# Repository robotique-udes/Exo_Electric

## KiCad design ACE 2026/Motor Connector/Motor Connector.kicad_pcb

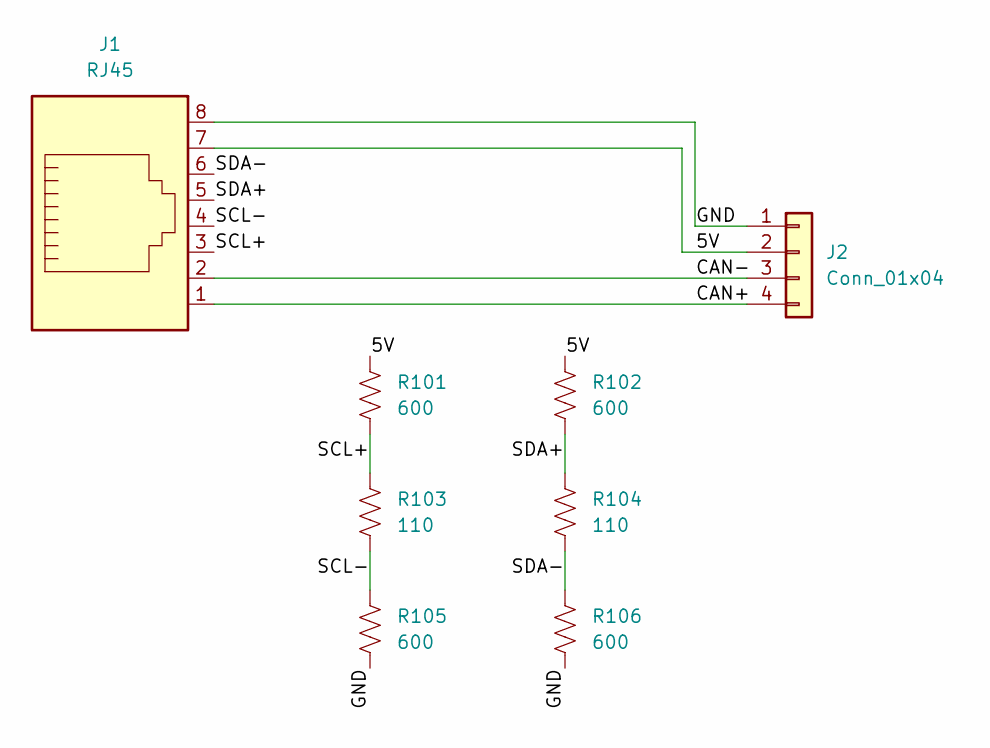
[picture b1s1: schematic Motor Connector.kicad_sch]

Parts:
J1: RJ45; RJ45_Amphenol_54602-x08_Horizontal
J2: Conn_01x04; SolderWire-0.75sqmm_1x04_P4.8mm_D1.25mm_OD2.3mm
R101, R102, R105, R106: 600; R_0805_2012Metric
R103, R104: 110; R_0805_2012Metric

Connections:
/5V: J1.7, J2.2, R101.1, R102.1
/CAN+: J1.1, J2.4
/CAN-: J1.2, J2.3
/GND: J1.8, J2.1, R105.2, R106.2
/SCL+: J1.3, R101.2, R103.1
/SCL-: J1.4, R103.2, R105.1
/SDA+: J1.5, R102.2, R104.1
/SDA-: J1.6, R104.2, R106.1

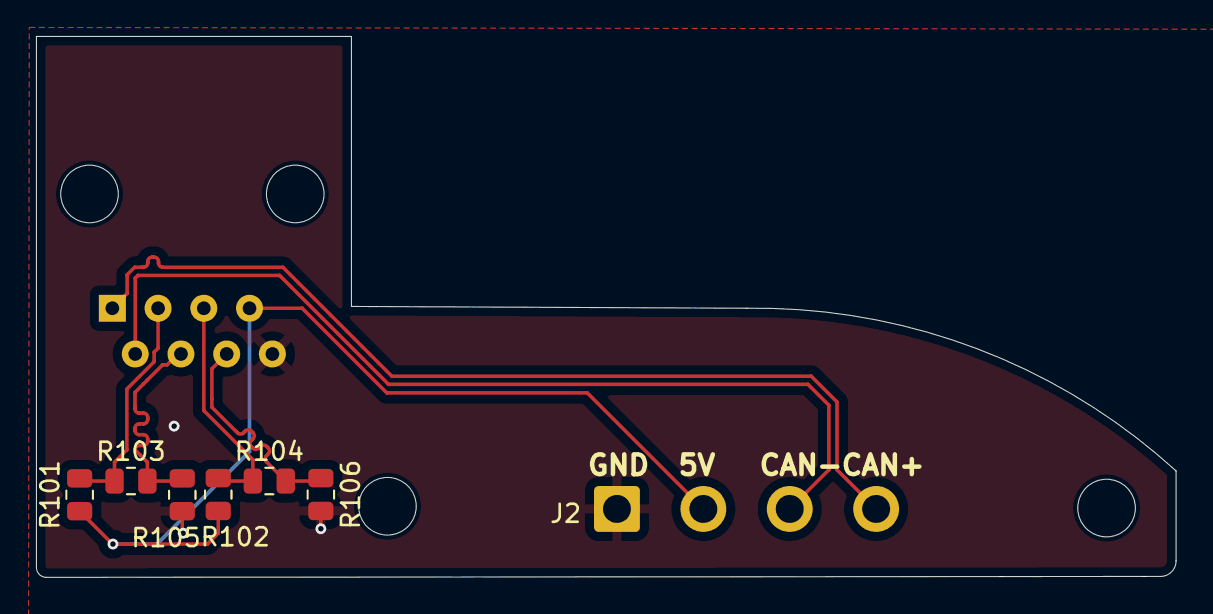
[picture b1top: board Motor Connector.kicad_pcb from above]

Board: 2 copper layers, 63.3 x 30.0 mm, 8 parts (1 on the bottom side), 8 nets.

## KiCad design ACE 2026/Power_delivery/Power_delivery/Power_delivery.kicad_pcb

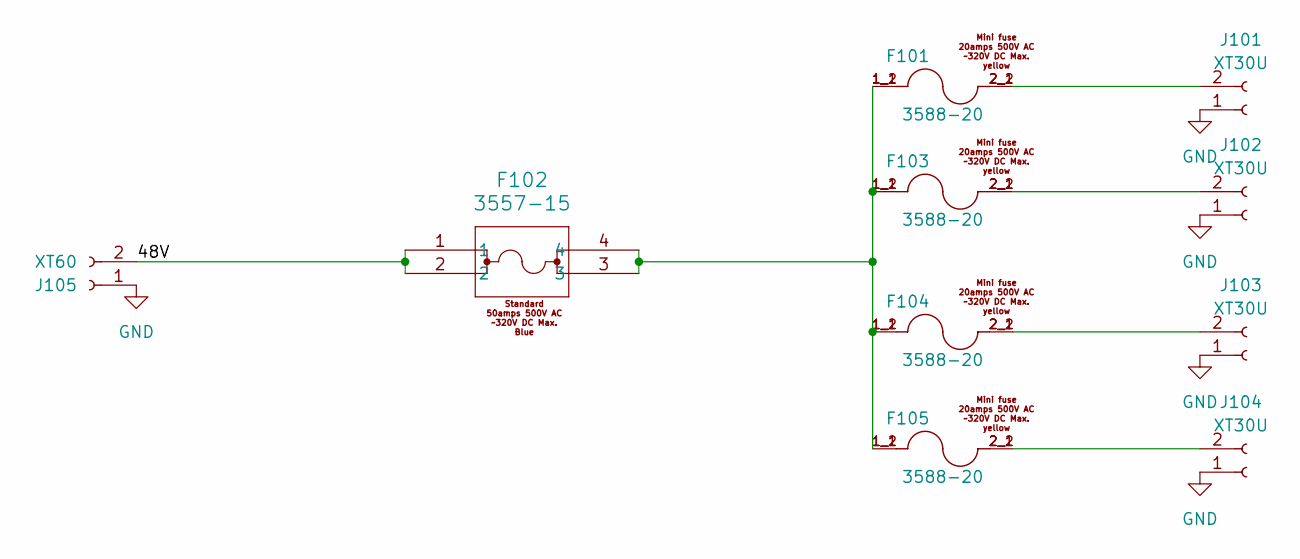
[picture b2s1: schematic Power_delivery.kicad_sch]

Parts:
F101, F103, F104, F105: 3588-20; FUSE_3588-20; PARTREV E
F102: 3557-15; 3557-15_KEY
J101, J102, J103, J104: XT30U; AMASS_XT30U-F_1x02_P5.0mm_Vertical
J105: XT60; AMASS_XT60-F_1x02_P7.20mm_Vertical

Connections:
/48V: F102.1, F102.2, J105.2
GND: J101.1, J102.1, J103.1, J104.1, J105.1
unnamed: F101.1_1, F101.1_2, F102.3, F102.4, F103.1_1, F103.1_2, F104.1_1, F104.1_2, F105.1_1, F105.1_2
unnamed: F101.2_1, F101.2_2, J101.2
unnamed: F103.2_1, F103.2_2, J102.2
unnamed: F104.2_1, F104.2_2, J103.2
unnamed: F105.2_1, F105.2_2, J104.2

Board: 4 copper layers, 10 parts (0 on the bottom side), 7 nets, no tracks yet.

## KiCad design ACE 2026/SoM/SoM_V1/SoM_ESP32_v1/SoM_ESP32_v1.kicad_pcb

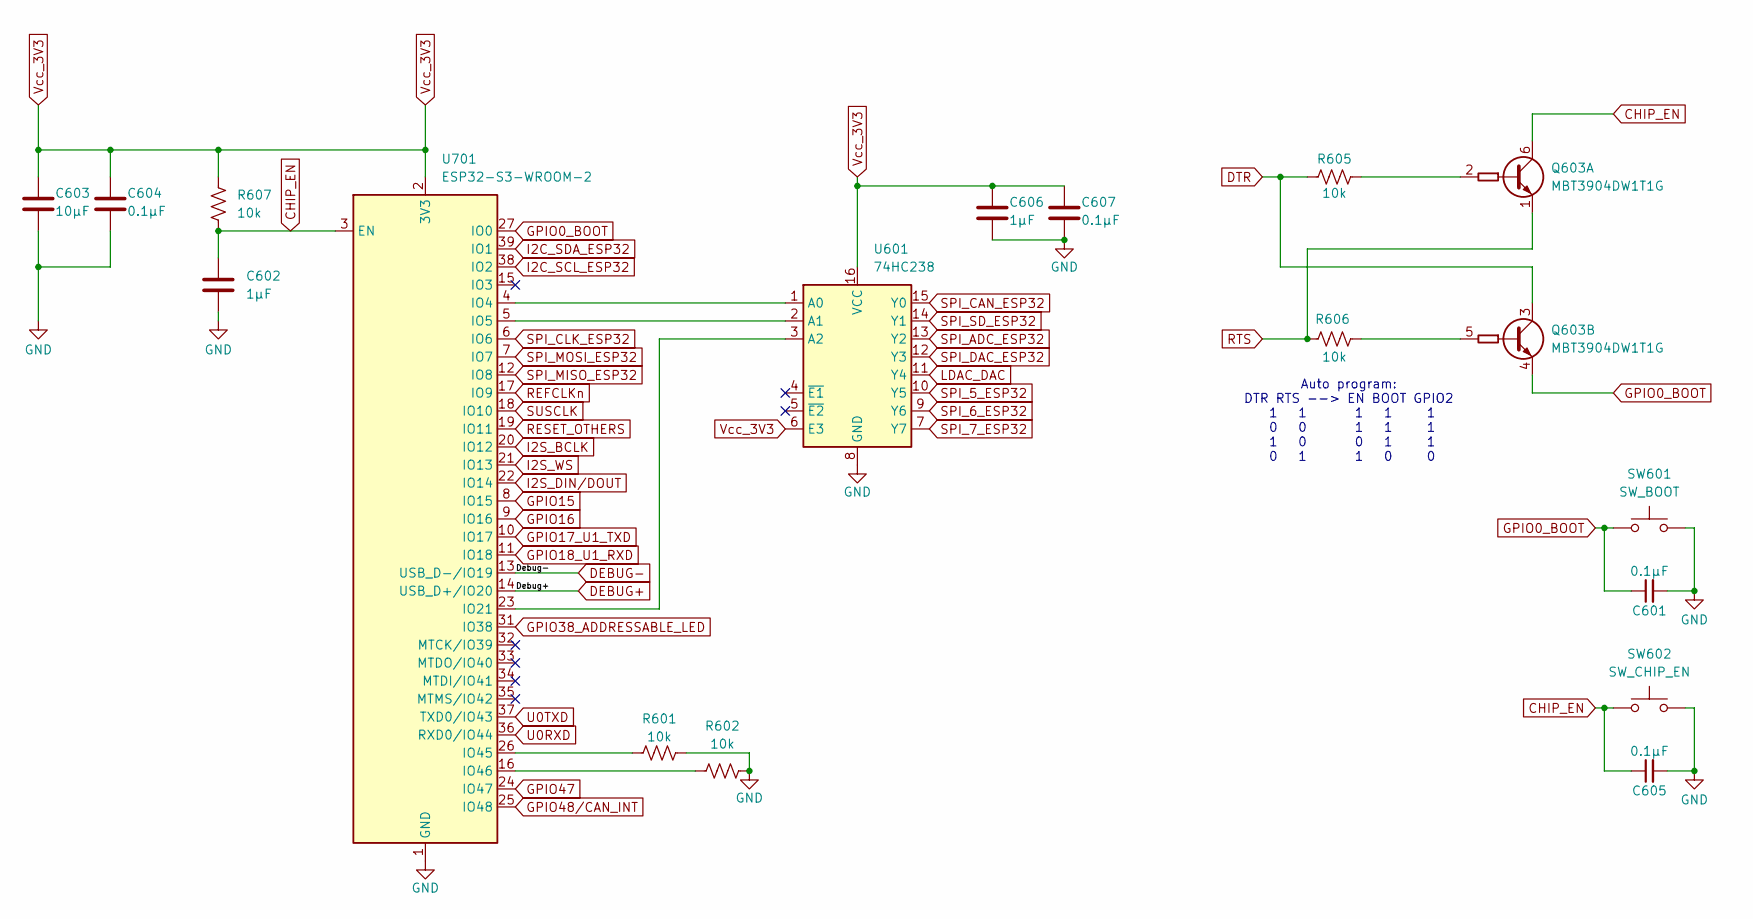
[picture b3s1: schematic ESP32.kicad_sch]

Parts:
C601, C604, C605, C607: 0.1µF; R_0805_2012Metric
C602, C606: 1µF; R_0805_2012Metric
C603: 10µF; R_0805_2012Metric
Q603: MBT3904DW1T1G; SOT-363_SC-70-6
R601, R602, R605, R606, R607: 10k; R_0805_2012Metric
SW601: SW_BOOT; SW_DIP_SPSTx01_Slide_6.7x4.1mm_W6.73mm_P2.54mm_LowProfile_J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
SW602: SW_CHIP_EN; SW_DIP_SPSTx01_Slide_6.7x4.1mm_W6.73mm_P2.54mm_LowProfile_J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
U601: 74HC238; SOIC-16_3.9x9.9mm_P1.27mm
U701: ESP32-S3-WROOM-2

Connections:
CHIP_EN: C602.1, C605.1, Q603.6 (C1), R607.2, SW602.1, U701.3 (EN); also elsewhere on the board
DEBUG+: U701.14 (USB_D+/IO20); also elsewhere on the board
DEBUG-: U701.13 (USB_D-/IO19); also elsewhere on the board
DTR: Q603.3 (C2), R605.1; also elsewhere on the board
GND: C601.2, C602.2, C603.2, C604.2, C605.2, C606.2, C607.2, R601.2, R602.2, SW601.2, SW602.2, U601.8 (GND), U701.1 (GND), U701.40 (GND), U701.41 (GND); also elsewhere on the board
GPIO0_BOOT: C601.1, Q603.4 (E2), SW601.1, U701.27 (IO0)
GPIO15: U701.8 (IO15); also elsewhere on the board
GPIO16: U701.9 (IO16); also elsewhere on the board
GPIO17_U1_TXD: U701.10 (IO17); also elsewhere on the board
GPIO18_U1_RXD: U701.11 (IO18); also elsewhere on the board
GPIO38_ADDRESSABLE_LED: U701.31 (IO38); also elsewhere on the board
GPIO47: U701.24 (IO47); also elsewhere on the board
GPIO48/CAN_INT: U701.25 (IO48); also elsewhere on the board
I2C_SCL_ESP32: U701.38 (IO2); also elsewhere on the board
I2C_SDA_ESP32: U701.39 (IO1); also elsewhere on the board
I2S_BCLK: U701.20 (IO12); also elsewhere on the board
I2S_DIN/DOUT: U701.22 (IO14); also elsewhere on the board
I2S_WS: U701.21 (IO13); also elsewhere on the board
LDAC_DAC: U601.11 (Y4); also elsewhere on the board
unnamed: Q603.2 (B1), R605.2
unnamed: Q603.5 (B2), R606.2
unnamed: U601.1 (A0), U701.4 (IO4)
unnamed: U601.2 (A1), U701.5 (IO5)
unnamed: U601.3 (A2), U701.23 (IO21)
unnamed: R601.1, U701.26 (IO45)
unnamed: R602.1, U701.16 (IO46)
REFCLKn: U701.17 (IO9)
RESET_OTHERS: U701.19 (IO11); also elsewhere on the board
RTS: Q603.1 (E1), R606.1; also elsewhere on the board
SPI_5_ESP32: U601.10 (Y5); also elsewhere on the board
SPI_6_ESP32: U601.9 (Y6); also elsewhere on the board
SPI_7_ESP32: U601.7 (Y7)
SPI_ADC_ESP32: U601.13 (Y2); also elsewhere on the board
SPI_CAN_ESP32: U601.15 (Y0); also elsewhere on the board
SPI_CLK_ESP32: U701.6 (IO6); also elsewhere on the board
SPI_DAC_ESP32: U601.12 (Y3); also elsewhere on the board
SPI_MISO_ESP32: U701.12 (IO8); also elsewhere on the board
SPI_MOSI_ESP32: U701.7 (IO7); also elsewhere on the board
SPI_SD_ESP32: U601.14 (Y1)
SUSCLK: U701.18 (IO10); also elsewhere on the board
U0RXD: U701.36 (RXD0/IO44); also elsewhere on the board
U0TXD: U701.37 (TXD0/IO43); also elsewhere on the board
Vcc_3V3: C603.1, C604.1, C606.1, C607.1, R607.1, U601.6 (E3), U601.16 (VCC), U701.2 (3V3); also elsewhere on the board

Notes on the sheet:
Auto program: DTR RTS --> EN BOOT GPIO2 1 1 1 1 1 0 0 1 1 1 1 0 0 1 1 0 1 1 0 0

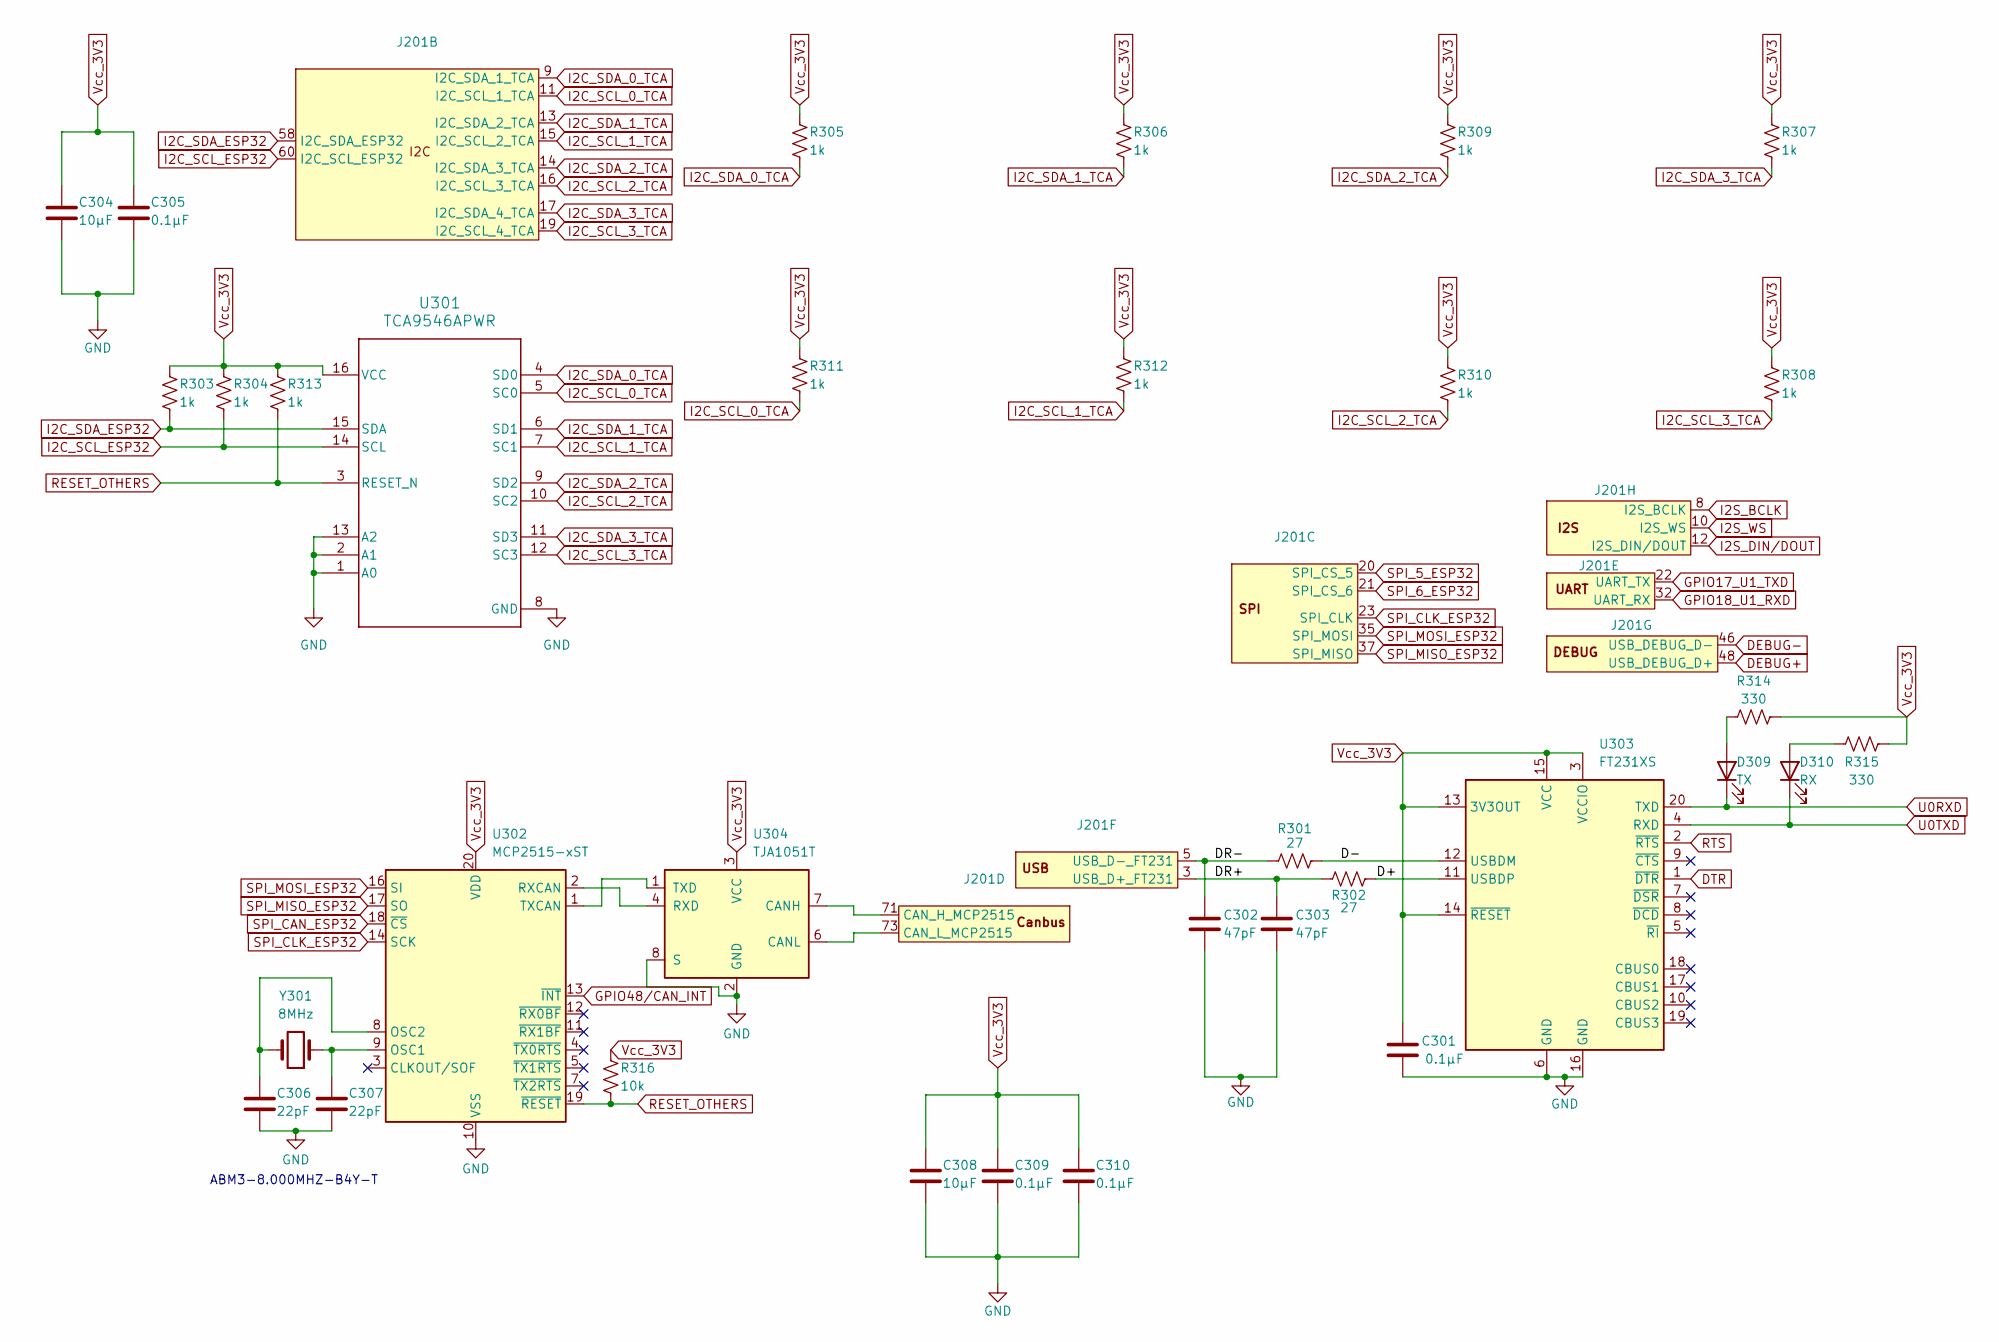
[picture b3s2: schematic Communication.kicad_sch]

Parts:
C301, C305, C309, C310: 0.1µF; R_0805_2012Metric
C302, C303: 47pF; R_0805_2012Metric
C304, C308: 10µF; R_0805_2012Metric
C306, C307: 22pF; R_0805_2012Metric
D309: TX; LED_0805_2012Metric
D310: RX; LED_0805_2012Metric
J201: NGFF_E
R301, R302: 27; R_0805_2012Metric
R303, R304, R305, R306, R307, R308, R309, R310, R311, R312, R313: 1k; R_0805_2012Metric
R314, R315: 330; R_0805_2012Metric
R316: 10k; R_0805_2012Metric
U301: TCA9546APWR; TSSOP-16_4.4x5mm_P0.65mm
U302: MCP2515-xST; TSSOP-20_4.4x6.5mm_P0.65mm
U303: FT231XS; SSOP-20_3.9x8.7mm_P0.635mm
U304: TJA1051T; SOIC-8_3.9x4.9mm_P1.27mm
Y301: 8MHz; Crystal_SMD_Abracon_ABM3-2Pin_5.0x3.2mm

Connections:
/Communication/D+: R302.2, U303.11 (USBDP)
/Communication/D-: R301.2, U303.12 (USBDM)
/Communication/DR+: C303.1, J201.3 (USB_D+_FT231), R302.1
/Communication/DR-: C302.1, J201.5 (USB_D-_FT231), R301.1
CHIP_EN: J201.56 (RESET_ESP32); also elsewhere on the board
DEBUG+: J201.48 (USB_DEBUG_D+); also elsewhere on the board
DEBUG-: J201.46 (USB_DEBUG_D-); also elsewhere on the board
DTR: U303.1 (~DTR); also elsewhere on the board
GND: C301.2, C302.2, C303.2, C304.2, C305.2, C306.2, C307.2, C308.2, C309.2, C310.2, J201.1 (GND), J201.7 (GND), J201.18 (GND), J201.33 (GND), J201.38 (GND), J201.39 (GND), J201.45 (GND), J201.51 (GND), J201.55 (GND), J201.57 (GND), J201.62 (GND), J201.63 (GND), J201.69 (GND), J201.75 (GND), U301.1 (A0), U301.2 (A1), U301.8 (GND), U301.13 (A2), U302.10 (VSS), U303.6 (GND), U303.16 (GND), U304.2 (GND), U304.8 (S); also elsewhere on the board
GPIO17_U1_TXD: J201.22 (UART_TX); also elsewhere on the board
GPIO18_U1_RXD: J201.32 (UART_RX); also elsewhere on the board
GPIO48/CAN_INT: U302.13 (~INT); also elsewhere on the board
I2C_SCL_0_TCA: J201.11 (I2C_SCL_1_TCA), R311.2, U301.5 (SC0)
I2C_SCL_1_TCA: J201.15 (I2C_SCL_2_TCA), R312.2, U301.7 (SC1)
I2C_SCL_2_TCA: J201.16 (I2C_SCL_3_TCA), R310.2, U301.10 (SC2)
I2C_SCL_3_TCA: J201.19 (I2C_SCL_4_TCA), R308.2, U301.12 (SC3)
I2C_SCL_ESP32: J201.60 (I2C_SCL_ESP32), R304.2, U301.14 (SCL); also elsewhere on the board
I2C_SDA_0_TCA: J201.9 (I2C_SDA_1_TCA), R305.2, U301.4 (SD0)
I2C_SDA_1_TCA: J201.13 (I2C_SDA_2_TCA), R306.2, U301.6 (SD1)
I2C_SDA_2_TCA: J201.14 (I2C_SDA_3_TCA), R309.2, U301.9 (SD2)
I2C_SDA_3_TCA: J201.17 (I2C_SDA_4_TCA), R307.2, U301.11 (SD3)
I2C_SDA_ESP32: J201.58 (I2C_SDA_ESP32), R303.2, U301.15 (SDA); also elsewhere on the board
I2S_BCLK: J201.8 (I2S_BCLK); also elsewhere on the board
I2S_DIN/DOUT: J201.12 (I2S_DIN/DOUT); also elsewhere on the board
I2S_WS: J201.10 (I2S_WS); also elsewhere on the board
unnamed 32: D309.2 (A), R314.1; also elsewhere on the board
unnamed 33: D310.2 (A), R315.1; also elsewhere on the board
unnamed: J201.71 (CAN_H_MCP2515), U304.7 (CANH)
unnamed: J201.73 (CAN_L_MCP2515), U304.6 (CANL)
unnamed: C307.1, U302.9 (OSC1), Y301.1
unnamed: C306.1, U302.8 (OSC2), Y301.2
unnamed: U302.2 (RXCAN), U304.4 (RXD)
unnamed: U302.1 (TXCAN), U304.1 (TXD)
RESET_OTHERS: J201.54 (RESET_AUTRES), R313.2, R316.2, U301.3 (RESET_N), U302.19 (~RESET); also elsewhere on the board
RTS: U303.2 (~RTS); also elsewhere on the board
SPI_5_ESP32: J201.20 (SPI_CS_1); also elsewhere on the board
SPI_6_ESP32: J201.21 (SPI_CS_2); also elsewhere on the board
SPI_CAN_ESP32: U302.18 (~CS); also elsewhere on the board
SPI_CLK_ESP32: J201.23 (SPI_CLK), U302.14 (SCK); also elsewhere on the board
SPI_MISO_ESP32: J201.37 (SPI_MISO), U302.17 (SO); also elsewhere on the board
SPI_MOSI_ESP32: J201.35 (SPI_MOSI), U302.16 (SI); also elsewhere on the board
U0RXD: D309.1 (K), U303.20 (TXD); also elsewhere on the board
U0TXD: D310.1 (K), U303.4 (RXD); also elsewhere on the board
Vcc_3V3: C301.1, C304.1, C305.1, C308.1, C309.1, C310.1, J201.2 (Vcc_3v3), J201.4 (Vcc_3v3), J201.72 (Vcc_3v3), J201.74 (Vcc_3v3), R303.1, R304.1, R305.1, R306.1, R307.1, R308.1, R309.1, R310.1, R311.1, R312.1, R313.1, R314.2, R315.2, R316.1, U301.16 (VCC), U302.20 (VDD), U303.3 (VCCIO), U303.13 (3V3OUT), U303.14 (~RESET), U303.15 (VCC), U304.3 (VCC); also elsewhere on the board

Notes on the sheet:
ABM3-8.000MHZ-B4Y-T

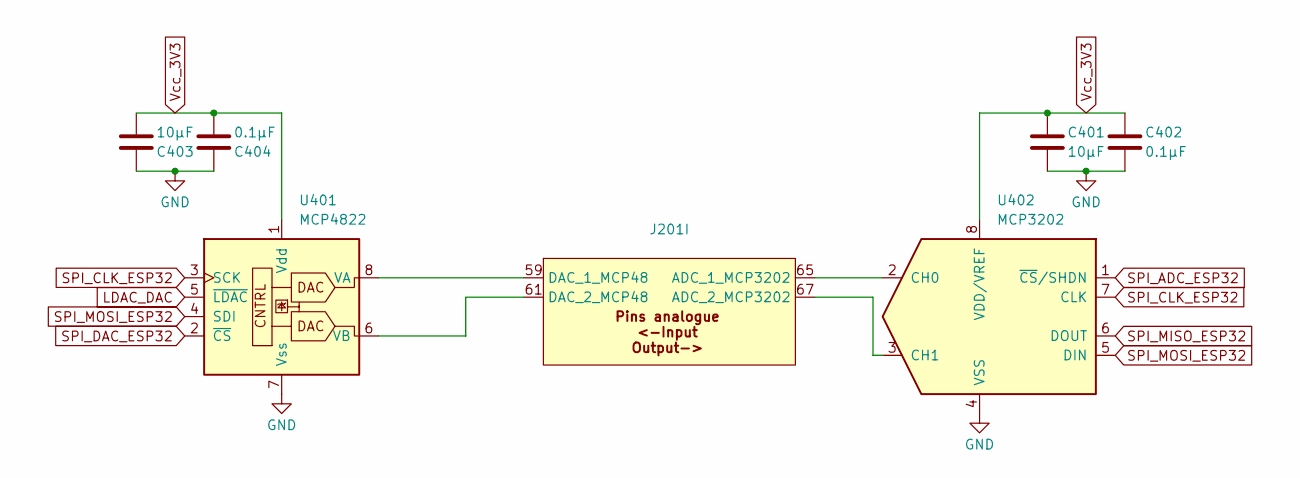
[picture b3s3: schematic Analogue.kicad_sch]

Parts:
C401, C403: 10µF; R_0805_2012Metric
C402, C404: 0.1µF; R_0805_2012Metric
J201: NGFF_E
U401: MCP4822; SOIC-8_3.9x4.9mm_P1.27mm
U402: MCP3202; SOIC-8_3.9x4.9mm_P1.27mm

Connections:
CHIP_EN: J201.56 (RESET_ESP32); also elsewhere on the board
GND: C401.2, C402.2, C403.1, C404.1, J201.1 (GND), J201.7 (GND), J201.18 (GND), J201.33 (GND), J201.38 (GND), J201.39 (GND), J201.45 (GND), J201.51 (GND), J201.55 (GND), J201.57 (GND), J201.62 (GND), J201.63 (GND), J201.69 (GND), J201.75 (GND), U401.7 (Vss), U402.4 (VSS); also elsewhere on the board
LDAC_DAC: U401.5 (~LDAC); also elsewhere on the board
unnamed: J201.65 (ADC_1_MCP3202), U402.2 (CH0)
unnamed: J201.67 (ADC_2_MCP3202), U402.3 (CH1)
unnamed: J201.59 (DAC_1_MCP48), U401.8 (VA)
unnamed: J201.61 (DAC_2_MCP48), U401.6 (VB)
RESET_OTHERS: J201.54 (RESET_AUTRES); also elsewhere on the board
SPI_ADC_ESP32: U402.1 (~CS/SHDN); also elsewhere on the board
SPI_CLK_ESP32: U401.3 (SCK), U402.7 (CLK); also elsewhere on the board
SPI_DAC_ESP32: U401.2 (~CS); also elsewhere on the board
SPI_MISO_ESP32: U402.6 (DOUT); also elsewhere on the board
SPI_MOSI_ESP32: U401.4 (SDI), U402.5 (DIN); also elsewhere on the board
Vcc_3V3: C401.1, C402.1, C403.2, C404.2, J201.2 (Vcc_3v3), J201.4 (Vcc_3v3), J201.72 (Vcc_3v3), J201.74 (Vcc_3v3), U401.1 (Vdd), U402.8 (VDD/VREF); also elsewhere on the board

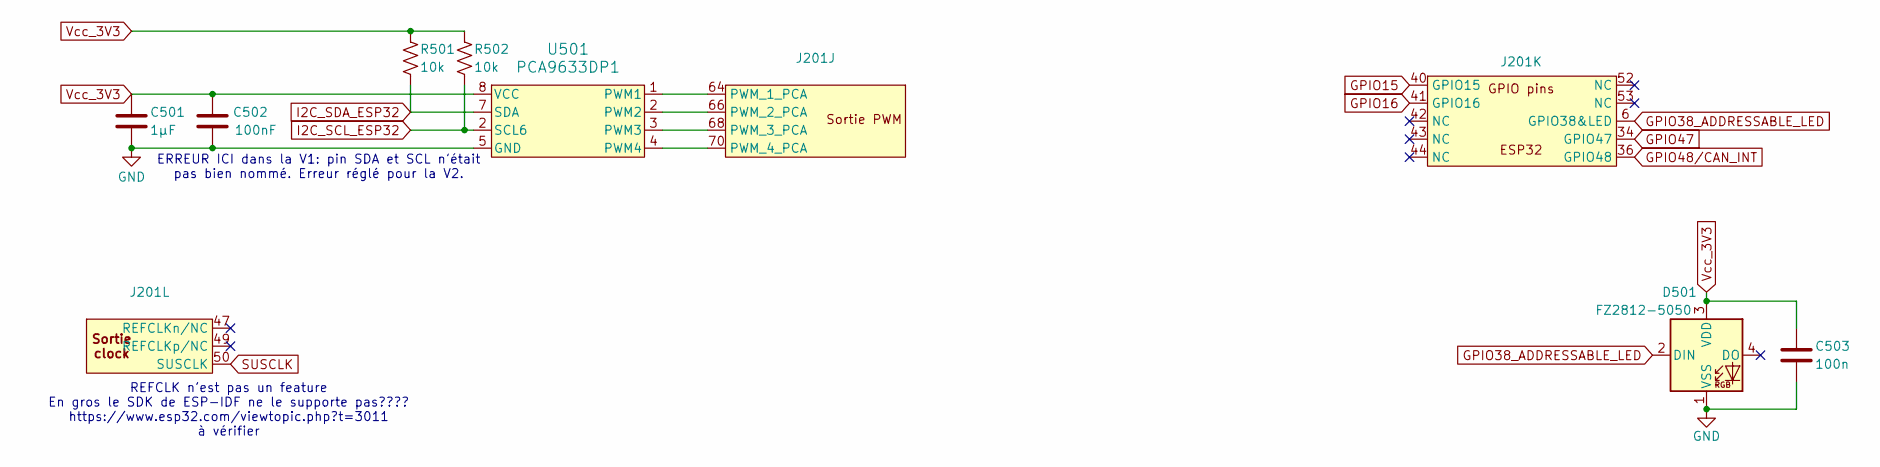
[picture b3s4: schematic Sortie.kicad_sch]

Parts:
C501: 1µF; R_0805_2012Metric
C502: 100nF; R_0805_2012Metric
C503: 100n; C_0805_2012Metric
D501: FZ2812-5050; LED_Inolux_IN-PI554FCH_PLCC4_5.0x5.0mm_P3.2mm
J201: NGFF_E
R501, R502: 10k; R_0805_2012Metric
U501: PCA9633DP1; SOT505-1_NXP

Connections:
CHIP_EN: J201.56 (RESET_ESP32); also elsewhere on the board
ESP32_SDA: R501.2, U501.7 (SDA)
GND: C501.2, C502.2, C503.2, D501.1 (VSS), J201.1 (GND), J201.7 (GND), J201.18 (GND), J201.33 (GND), J201.38 (GND), J201.39 (GND), J201.45 (GND), J201.51 (GND), J201.55 (GND), J201.57 (GND), J201.62 (GND), J201.63 (GND), J201.69 (GND), J201.75 (GND), U501.5 (GND); also elsewhere on the board
GPIO15: J201.40 (GPIO15); also elsewhere on the board
GPIO16: J201.41 (GPIO16); also elsewhere on the board
GPIO38_ADDRESSABLE_LED: D501.2 (DIN), J201.6 (GPIO38&LED); also elsewhere on the board
GPIO47: J201.34 (GPIO47); also elsewhere on the board
GPIO48/CAN_INT: J201.36 (GPIO48); also elsewhere on the board
unnamed: J201.64 (PWM_1_PCA), U501.1 (PWM1)
unnamed: J201.68 (PWM_3_PCA), U501.3 (PWM3)
unnamed: J201.70 (PWM_4_PCA), U501.4 (PWM4)
RESET_OTHERS: J201.54 (RESET_AUTRES); also elsewhere on the board
SUSCLK: J201.50 (SUSCLK); also elsewhere on the board
Vcc_3V3: C501.1, C502.1, C503.1, D501.3 (VDD), J201.2 (Vcc_3v3), J201.4 (Vcc_3v3), J201.72 (Vcc_3v3), J201.74 (Vcc_3v3), R501.1, R502.1, U501.8 (VCC); also elsewhere on the board

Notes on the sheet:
ERREUR ICI dans la V1: pin SDA et SCL n'était pas bien nommé. Erreur réglé pour la V2.
REFCLK n'est pas un feature En gros le SDK de ESP-IDF ne le supporte pas???? https://www.esp32.com/viewtopic.php?t=3011 à vérifier

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
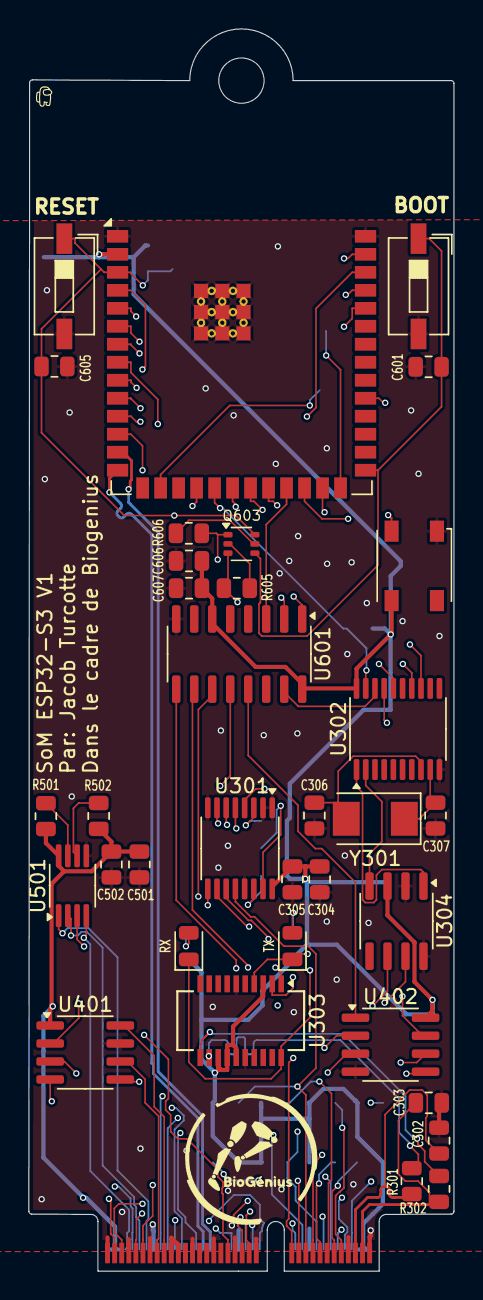
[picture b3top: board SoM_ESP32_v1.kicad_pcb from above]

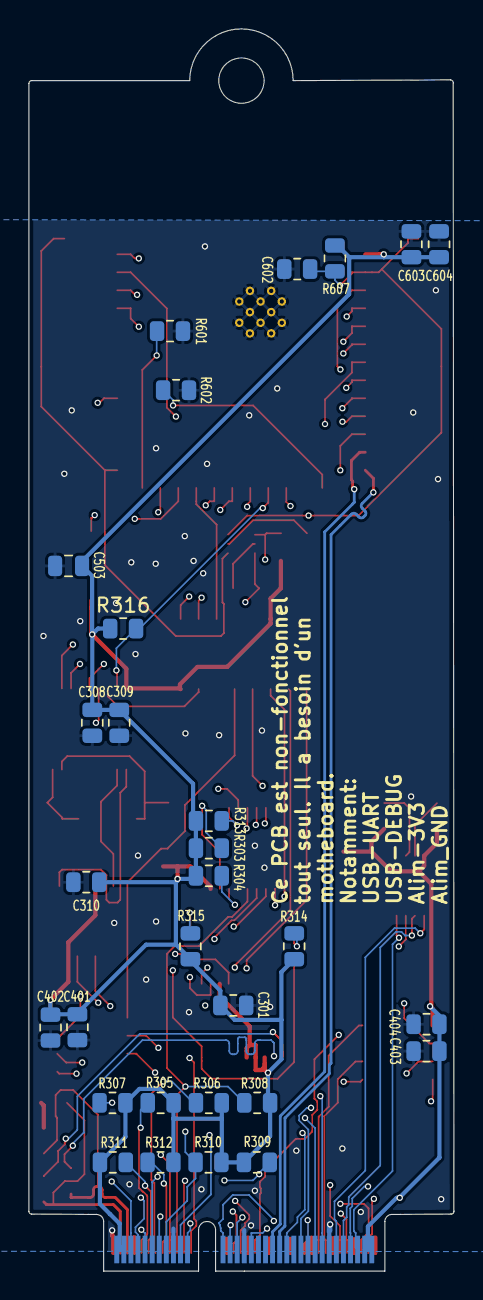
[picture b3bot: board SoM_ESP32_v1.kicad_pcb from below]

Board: 4 copper layers, 30.0 x 87.7 mm, 64 parts (29 on the bottom side), 70 nets.

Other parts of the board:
RX: TX; LED_0805_2012Metric
TX: RX; LED_0805_2012Metric

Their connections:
unnamed 32: RX.2 (A); also elsewhere on the board
unnamed 33: TX.2 (A); also elsewhere on the board
U0RXD: RX.1 (K); also elsewhere on the board
U0TXD: TX.1 (K); also elsewhere on the board

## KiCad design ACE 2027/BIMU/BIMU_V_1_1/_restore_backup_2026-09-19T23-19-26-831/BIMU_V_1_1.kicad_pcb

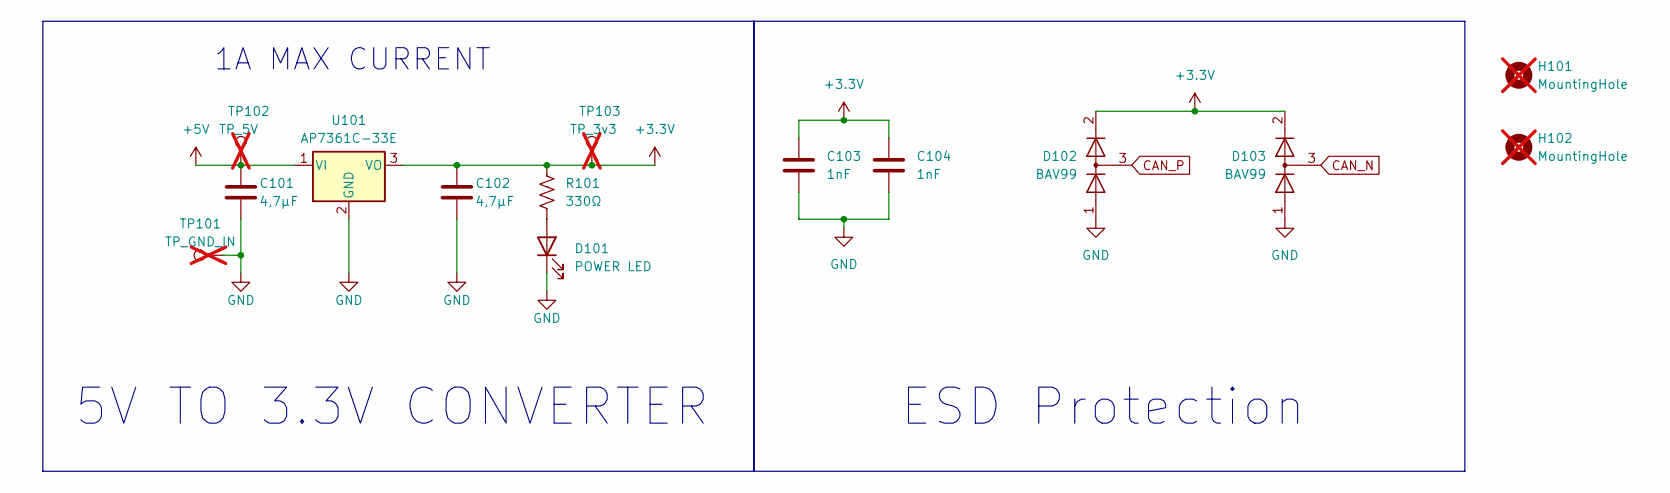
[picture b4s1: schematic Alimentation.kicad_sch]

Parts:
C101, C102: 4,7µF; C_0805_2012Metric_Pad1.18x1.45mm_HandSolder; Digi-Key_PN 1276-2970-1-ND
C103, C104: 1nF; C_1812_4532Metric_Pad1.57x3.40mm_HandSolder; Digi-Key_PN 399-C1812C104MDRACTUCT-ND
D101: POWER LED; LED_0805_2012Metric_Pad1.15x1.40mm_HandSolder; Digi-Key_PN 1516-QBLP631-IG5CT-ND
D102, D103: BAV99; SOT-23; Digi-Key_PN 1655-BAV99CT-ND
H101, H102: MountingHole; MountingHole_3.2mm_M3_ISO14580; not fitted
R101: 330Ω; R_0805_2012Metric_Pad1.20x1.40mm_HandSolder; Digi-Key_PN 541-4168-1-ND
TP101: TP_GND_IN; TestPoint_Pad_1.0x1.0mm; not fitted
TP102: TP_5V; TestPoint_Pad_1.0x1.0mm; not fitted
TP103: TP_3v3; TestPoint_Pad_1.0x1.0mm; not fitted
U101: AP7361C-33E; SOT-223-3_TabPin2; Digi-Key_PN AP7361C-33E-13DICT-ND

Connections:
+3.3V: C102.2, C103.1, C104.1, D102.2 (A), D103.2 (A), R101.1, TP103.1 (1_1), U101.3 (VO); also elsewhere on the board
+5V: C101.2, TP102.1 (1_1), U101.1 (VI); also elsewhere on the board
CAN_N: D103.3 (K); also elsewhere on the board
CAN_P: D102.3 (K); also elsewhere on the board
GND: C101.1, C102.1, C103.2, C104.2, D101.1 (K), D102.1 (K), D103.1 (K), TP101.1 (1_1), U101.2 (GND); also elsewhere on the board
unnamed: D101.2 (A), R101.2

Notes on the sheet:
ESD Protection
1A MAX CURRENT
5V TO 3.3V CONVERTER
